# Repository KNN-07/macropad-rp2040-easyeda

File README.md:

# MACRO12 RP2040 macro pad for EasyEDA Pro

An editable EasyEDA Pro adaptation of the Adafruit MacroPad RP2040 Rev D: 12 MX-compatible hot-swap keys in a 3-column by 4-row layout, onboard RP2040, and USB-C.

Assembled Rev C prototype visualization using the actual board layout and CAD component models. Keycaps, knob, colors and displayed UI are illustrative. [Editable Blender scene, model sources and reproduction instructions](hardware/3d/).

**Rev C is released for first-article bare-board fabrication with the specified manufacturing and assembly constraints.** Native electrical DRC and schematic comparison pass; independent checks confirm all 76 nets, 338 physical pads and 171 drilled features. Nine intentional mechanical overlap findings remain documented individually in the [mechanical review](docs/mechanical-review.md). No physical board has been assembled or powered.

Download the [fabrication ZIP](fabrication/MACRO12-RevC-Gerber.zip) and read the [fabrication settings](docs/fabrication-notes.md) before ordering. The 1.6 mm board, precision LED milling and OLED/mounting controls are part of the design.

These previews are rendered from the released manufacturing data.

## Hardware

| Item | Design |
| --- | --- |
| Keys | 12, 19.05 mm pitch, MX-compatible hot-swap sockets |
| Controller | Onboard RP2040 with external flash |
| USB | HRO TYPE-C-31-M-12 USB-C connector |
| Encoder | Bourns PEC11R-4215F-S0024 with push switch |
| Board | 59.69 x 104.14 mm, two copper layers |
| Retained upstream features | 12 reverse-mount RGB LEDs, 16-pin folding OLED panel, speaker/amplifier, STEMMA QT |

The keys connect individually to GPIO1 through GPIO12; they are not a matrix. The electronic circuit and pin assignments come from the upstream Adafruit Rev D source. [QMK firmware with VIA support](firmware/README.md) provides four layers, remappable keys and encoder, RGB effects, and OLED status. Physical firmware testing remains pending.

## Open and edit

Import [MACRO12-RevC.epro](hardware/easyeda/MACRO12-RevC.epro) in EasyEDA Pro using **File > Import > EasyEDA (Professional)**. The archive includes the two schematic sheets, PCB, symbols, and footprints. Preserve the supplied footprints when importing; automatic footprint reassociation can change the design.

The EasyEDA project is the revised canonical design. The EAGLE files in `hardware/upstream/` are the unmodified upstream Rev D reference and do not contain the revised routing or Rev C footprint corrections. Earlier Rev B RC1 exports are superseded.

## Files

- [`hardware/easyeda/`](hardware/easyeda/): editable revised project.
- [`hardware/3d/`](hardware/3d/): assembled visualization, editable Blender scene, source CAD and render script.
- [`firmware/`](firmware/): QMK source, VIA definition, build workflow, flashing instructions, and first-article checks.
- [`fabrication/`](fabrication/): reviewed Gerber/Excellon ZIP and its ten unmodified manufacturing files.
- [`hardware/upstream/`](hardware/upstream/): original Rev D board and schematic, full upstream README, license, and its referenced product image.
- [`bom/`](bom/): reference BOM with Rev C part selections and retained upstream metadata. This is not an assembly-approved BOM or placement file.
- [`docs/release-validation.md`](docs/release-validation.md): completed checks, documented exceptions, and prototype validation limits.
- [`docs/mechanical-review.md`](docs/mechanical-review.md): drawing review, footprint corrections, and nine individual DRC dispositions.
- [`docs/assembly.md`](docs/assembly.md): required mounting and OLED-insulation controls.
- [`docs/fabrication-notes.md`](docs/fabrication-notes.md): board, milling, and plated-slot requirements.
- [`docs/modifications.md`](docs/modifications.md): changes from the upstream hardware.
- [`docs/checksums.sha256`](docs/checksums.sha256): file integrity hashes for the published snapshot.

## Attribution and license

Derived from [Adafruit MacroPad RP2040 PCB](https://github.com/adafruit/Adafruit-MacroPad-RP2040-PCB), designed by Limor Fried/Ladyada for Adafruit Industries, at commit `fdd7f2cb3bc2b3c7a9c0765780387647ea872141`.

The hardware design and modifications are distributed under **Creative Commons Attribution-ShareAlike 3.0 Unported**; see [LICENSE](LICENSE). The original [upstream README](hardware/upstream/README.md) is included in full as required by its redistribution notice. Hardware documentation uses the same license. The assembled visualization includes MIT-licensed Adafruit CAD; see [3D model licensing](hardware/3d/README.md#sources-and-licenses). Firmware, its documentation and tooling use **GPL-2.0-or-later**; see [firmware licensing](firmware/README.md#license-and-source). Adafruit and Raspberry Pi names identify the upstream design and component platform; this adaptation is not an official Adafruit product.

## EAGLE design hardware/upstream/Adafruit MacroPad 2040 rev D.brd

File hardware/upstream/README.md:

## Adafruit MacroPad RP2040 PCB

<a href="http://www.adafruit.com/products/5100"><br/>
Click here to purchase one from the Adafruit shop</a>

PCB files for the Adafruit MacroPad RP2040. 

Format is EagleCAD schematic and board layout
* https://www.adafruit.com/product/5100

### Description

Strap yourself in, we're launching in T-minus 10 seconds...Destination? A new Class M planet called MACROPAD! M here, stands for Microcontroller because this 3x4 keyboard controller features the newest technology from the Raspberry Pi sector: say hello to the RP2040. It's speedy little microcontroller with lots of GPIO pins and a 64 times more RAM than the Apollo Guidance Computer. We added 8 MB of flash memory for plenty of storage.

This is just the bare MACROPAD PCB assembly! Many folks in the mechanical keyboard community like to customize the keys and keycaps of their keebs, so this is sold 'bare bones' here. To use as a full product you'll need to add 12 MX-compatible key switches and matching key caps.

Get ready to upgrade your desk's mission control station with a CircuitPython or Arduino powered Macropad - complete with 12 buttons, OLED display, speaker and rotary encoder. Customize it for your spacecraft to help guide you through the great reaches of the unknown. (Or just have it type out your favorite emojis.)

Each of the 12 sockets can accept a Cherry MX-compatible key switch. No soldering required, just snap it in! Use any key switch you like - but we recommend ones with slots that will allow the matching twelve NeoPixels underneath to shine through.

This space-ship is also fitted with a 128x64 monochome OLED for a crisp heads-up display that can be used in Arduino or CircuitPython to display keymaps, stats, computer performance, etc. There's also a rotary encoder with push-button soldered in. Twist and turn it or push to change volume or monitor brightness or scroll: whatever you like! A tiny speaker can give audio feedback or play fun bleepy tunes.

Want to add more hardware? No worries - a STEMMA QT port on the side lets you connect any I2C add-on peripherals from the massive STEMMA QT / Qwiic family of plug in boards.

Please note, the RP2040 chip does not currently have QMK support - this macropad is designed to be programmed in Arduino or CircuitPython! If QMK eventually does add RP2040 as a supported chipset (no ETA and no plans that we know of), we'll update this page.

TL;DR?

* Raspberry Pi RP2040 Chip + 8MB Flash memory - Dual core Cortex M0+ at ~130MHz with 264KB or RAM. Runs CircuitPython, Arduino or MicroPython with ease and lots of space for development code and files
* USB C Connector for Power/Data - of course this can act as an HID device but also can be MIDI, UART, etc.
* 3x4 Mechanical key switch sockets - accepts any Cherry MX-compatible switches. Individually tied to GPIO pins (not matrix wired)
* One NeoPixel RGB LED per switch, on north side
* Rotary encoder, 20 detents per rotation, with push-switch on GPIO pin. Push switch is also used for entering bootloader mode when held down on power-up or reset.
* 128x64 SH1106 Monochrome OLED display - On high speed hardware SPI port for quick updates
* 8mm Speaker/Buzzer - With Class D amplifier and RC filter, can be used to make simple beeps and sounds effects.
* STEMMA QT Connector - Allows adding any I2C sensors/displays/devices with plug-and-play cables.
* Reset button - On the side, for quick restarting of code

### License

Adafruit invests time and resources providing this open source design, please support Adafruit and open-source hardware by purchasing products from [Adafruit](https://www.adafruit.com)!

Designed by Limor Fried/Ladyada for Adafruit Industries.

Creative Commons Attribution/Share-Alike, all text above must be included in any redistribution. 
See license.txt for additional details.

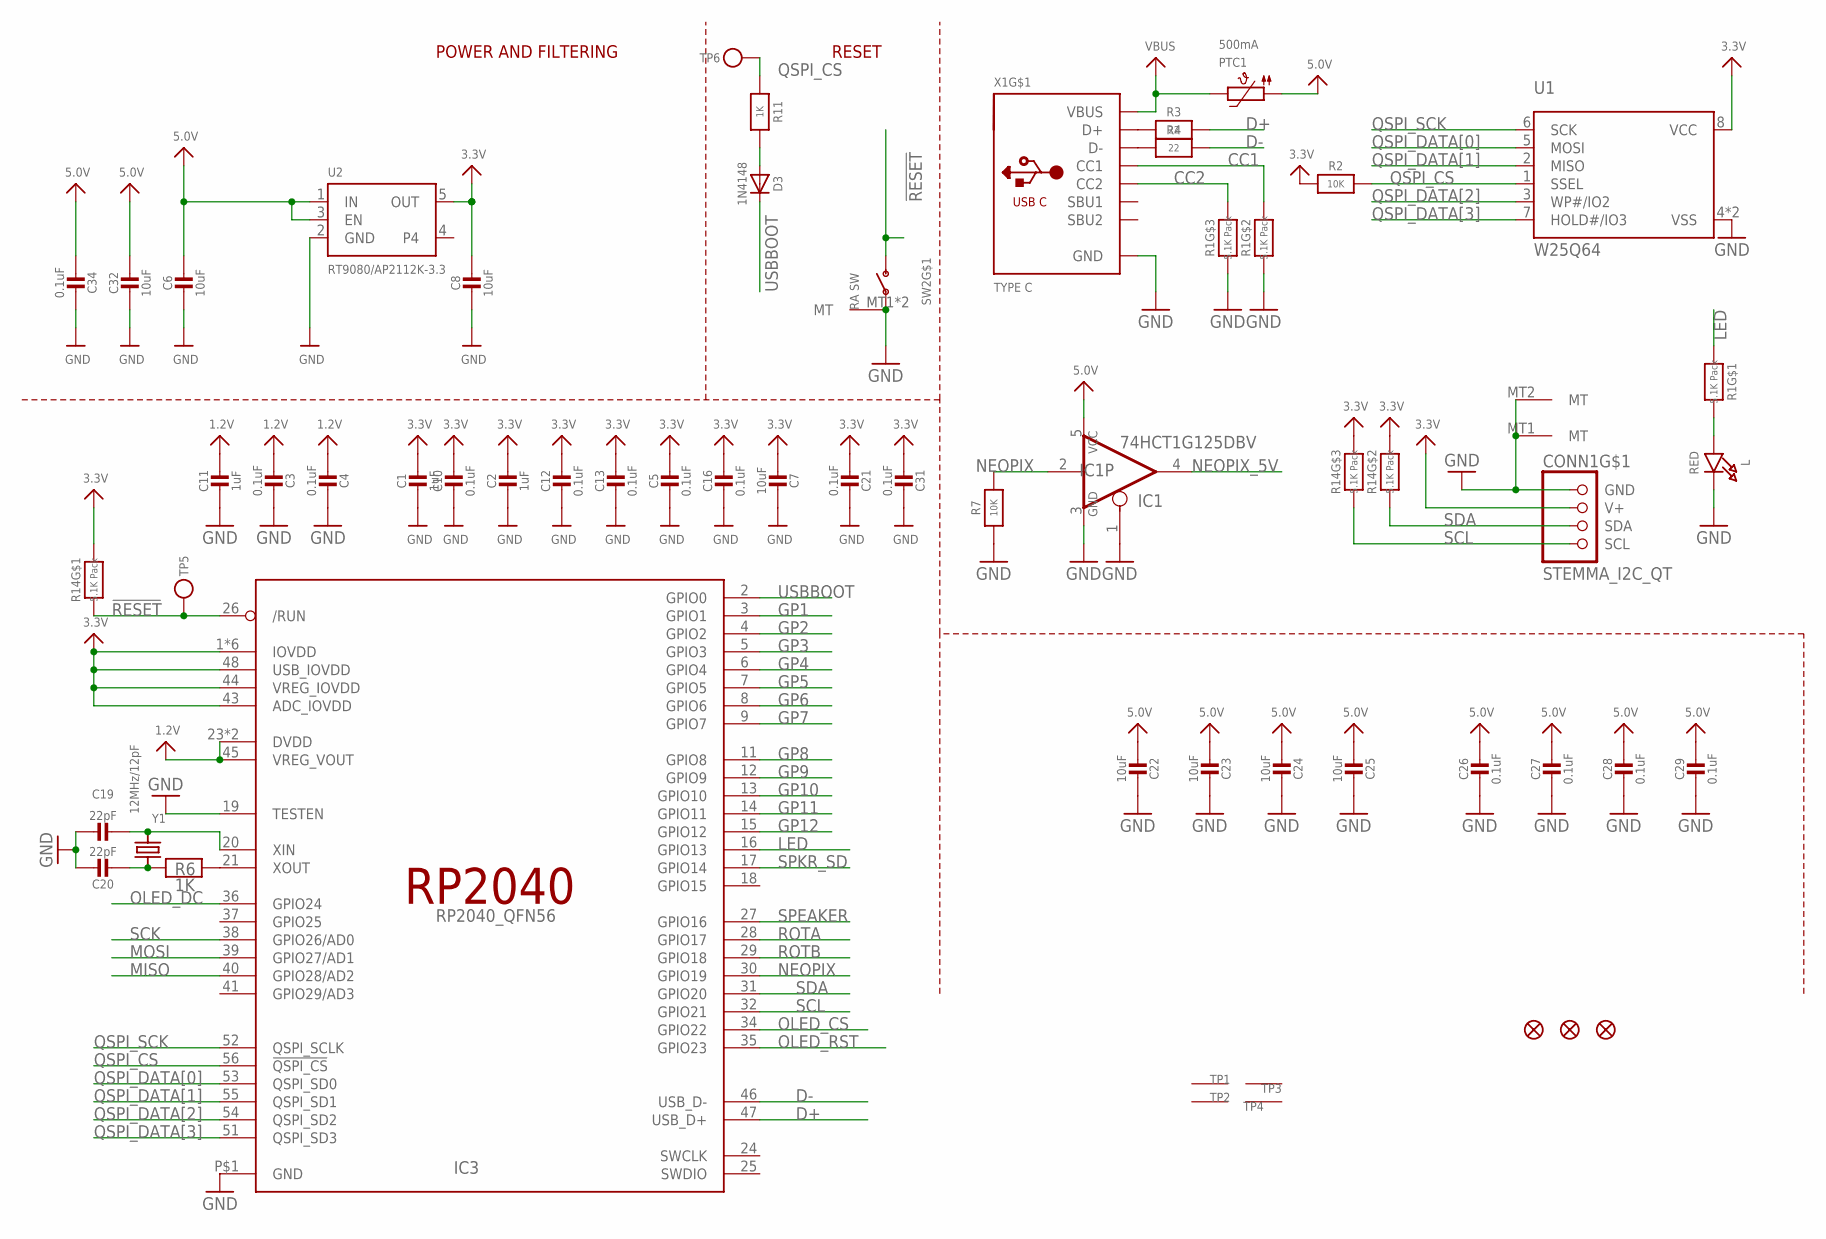
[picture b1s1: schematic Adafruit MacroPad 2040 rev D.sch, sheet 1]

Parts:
C1, C2, C11: 1uF; 0603-NO
C3, C4, C5, C10, C12, C13, C16, C21, C26, C27, C28, C29, C31, C34: 0.1uF; 0603-NO
C6, C7, C8, C22, C23, C24, C25, C32: 10uF; 0805-NO
C19, C20: 22pF; 0603-NO
CONN1: STEMMA_I2C_QT; JST_SH4
D3: 1N4148; SOD-323
IC1: 74HCT1G125DBV; SOT23-5
IC3: RP2040_QFN56; QFN56_7MM_REDUCEDEPAD
L: RED; CHIPLED_0603_NOOUTLINE
PTC1: 500mA; 0805-NO
R1, R14: 5.1K Pack; RESPACK_4X0603
R2, R7: 10K; 0603-NO
R3, R4: 22; 0603-NO
R6, R11: 1K; 0603-NO
SW2: RA SW; SPST_TACTILE_RA
TP1, TP2, TP3, TP4: SEWTAP_SMTNUTM3; SMT_NUT_3MM
TP5, TP6: TESTPOINTROUND1.5MMNO; TESTPOINT_ROUND_1.5MM_NO
U1: W25Q64; USON8_4X4
U2: RT9080/AP2112K-3.3; SOT23-5; JLC_ROTATION 0
U$34, U$35, U$80: FIDUCIAL_1MM
X1: TYPE C; USB_C_CUSB31-CFM2AX-01-X
Y1: 12MHz/12pF; CRYSTAL_2.5X2

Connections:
1.2V: C3.2, C4.2, C11.1, IC3.23 (DVDD), IC3.45 (VREG_VOUT), IC3.50 (DVDD)
3.3V: C1.1, C2.1, C5.1, C7.2, C8.1, C10.1, C12.1, C13.1, C16.1, C21.2, C31.2, CONN1.2 (V+), IC3.1 (IOVDD), IC3.10 (IOVDD), IC3.22 (IOVDD), IC3.33 (IOVDD), IC3.42 (IOVDD), IC3.43 (ADC_IOVDD), IC3.44 (VREG_IOVDD), IC3.48 (USB_IOVDD), IC3.49 (IOVDD), R2.1, R14.6 (2), R14.7 (2), R14.8 (2), U1.8 (VCC), U2.5 (OUT); also elsewhere on the board
5.0V: C6.1, C22.2, C23.2, C24.2, C25.2, C26.1, C27.1, C28.1, C29.1, C32.1, C34.2, IC1.5 (VCC), PTC1.1, U2.1 (IN), U2.3 (EN); also elsewhere on the board
!RESET: IC3.26 (/RUN), R14.1, SW2.2 (S), TP5.P$1
CC1: R1.7 (2), X1.A5 (CC1)
CC2: R1.6 (2), X1.B5 (CC2)
D+: IC3.47 (USB_D+), R3.2
D-: IC3.46 (USB_D-), R4.2
GND: C1.2, C2.2, C3.1, C4.1, C5.2, C6.2, C7.1, C8.2, C10.2, C11.2, C12.2, C13.2, C16.2, C19.1, C20.1, C21.1, C22.1, C23.1, C24.1, C25.1, C26.2, C27.2, C28.2, C29.2, C31.1, C32.2, C34.1, CONN1.1 (GND), CONN1.MT1 (MT), CONN1.MT2 (MT), IC1.1 (OE), IC1.3 (GND), IC3.19 (TESTEN), IC3.P$1 (GND), L.C, R1.2 (1), R1.3 (1), R7.1, SW2.1, SW2.MT1 (MT), SW2.MT2 (MT), U1.4 (VSS), U1.PAD (VSS), U2.2 (GND), X1.A1B12 (GND), X1.B1A12 (GND); also elsewhere on the board
GP1: IC3.3 (GPIO1); also elsewhere on the board
GP2: IC3.4 (GPIO2); also elsewhere on the board
GP3: IC3.5 (GPIO3); also elsewhere on the board
GP4: IC3.6 (GPIO4); also elsewhere on the board
GP5: IC3.7 (GPIO5); also elsewhere on the board
GP6: IC3.8 (GPIO6); also elsewhere on the board
GP7: IC3.9 (GPIO7); also elsewhere on the board
GP8: IC3.11 (GPIO8); also elsewhere on the board
GP9: IC3.12 (GPIO9); also elsewhere on the board
GP10: IC3.13 (GPIO10); also elsewhere on the board
GP11: IC3.14 (GPIO11); also elsewhere on the board
GP12: IC3.15 (GPIO12); also elsewhere on the board
LED: IC3.16 (GPIO13), R1.1
MISO: IC3.40 (GPIO28/AD2)
MOSI: IC3.39 (GPIO27/AD1); also elsewhere on the board
unnamed: R3.1, X1.A6 (D+), X1.B6 (D+)
unnamed: L.A, R1.8 (2)
unnamed: R4.1, X1.A7 (D-), X1.B7 (D-)
unnamed: D3.A, R11.2
unnamed: C19.2, IC3.20 (XIN), Y1.3 (2)
unnamed: C20.2, R6.1, Y1.1
unnamed: IC3.21 (XOUT), R6.2
NEOPIX: IC1.2 (I), IC3.30 (GPIO19), R7.2
NEOPIX_5V: IC1.4 (O); also elsewhere on the board
OLED_CS: IC3.34 (GPIO22); also elsewhere on the board
OLED_DC: IC3.36 (GPIO24); also elsewhere on the board
OLED_RST: IC3.35 (GPIO23); also elsewhere on the board
QSPI_CS: IC3.56 (!QSPI_CS), R2.2, R11.1, TP6.P$1, U1.1 (SSEL)
QSPI_DATA[0]: IC3.53 (QSPI_SD0), U1.5 (MOSI)
QSPI_DATA[1]: IC3.55 (QSPI_SD1), U1.2 (MISO)
QSPI_DATA[2]: IC3.54 (QSPI_SD2), U1.3 (WP#/IO2)
QSPI_DATA[3]: IC3.51 (QSPI_SD3), U1.7 (HOLD#/IO3)
QSPI_SCK: IC3.52 (QSPI_SCLK), U1.6 (SCK)
ROTA: IC3.28 (GPIO17); also elsewhere on the board
ROTB: IC3.29 (GPIO18); also elsewhere on the board
SCK: IC3.38 (GPIO26/AD0); also elsewhere on the board
SCL: CONN1.4 (SCL), IC3.32 (GPIO21), R14.3 (1)
SDA: CONN1.3 (SDA), IC3.31 (GPIO20), R14.2 (1)
SPEAKER: IC3.27 (GPIO16); also elsewhere on the board
SPKR_SD: IC3.17 (GPIO14); also elsewhere on the board
USBBOOT: D3.C, IC3.2 (GPIO0); also elsewhere on the board
VBUS: PTC1.2, X1.A4B9 (VBUS), X1.B4A9 (VBUS)

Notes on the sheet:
POWER AND FILTERING
RESET

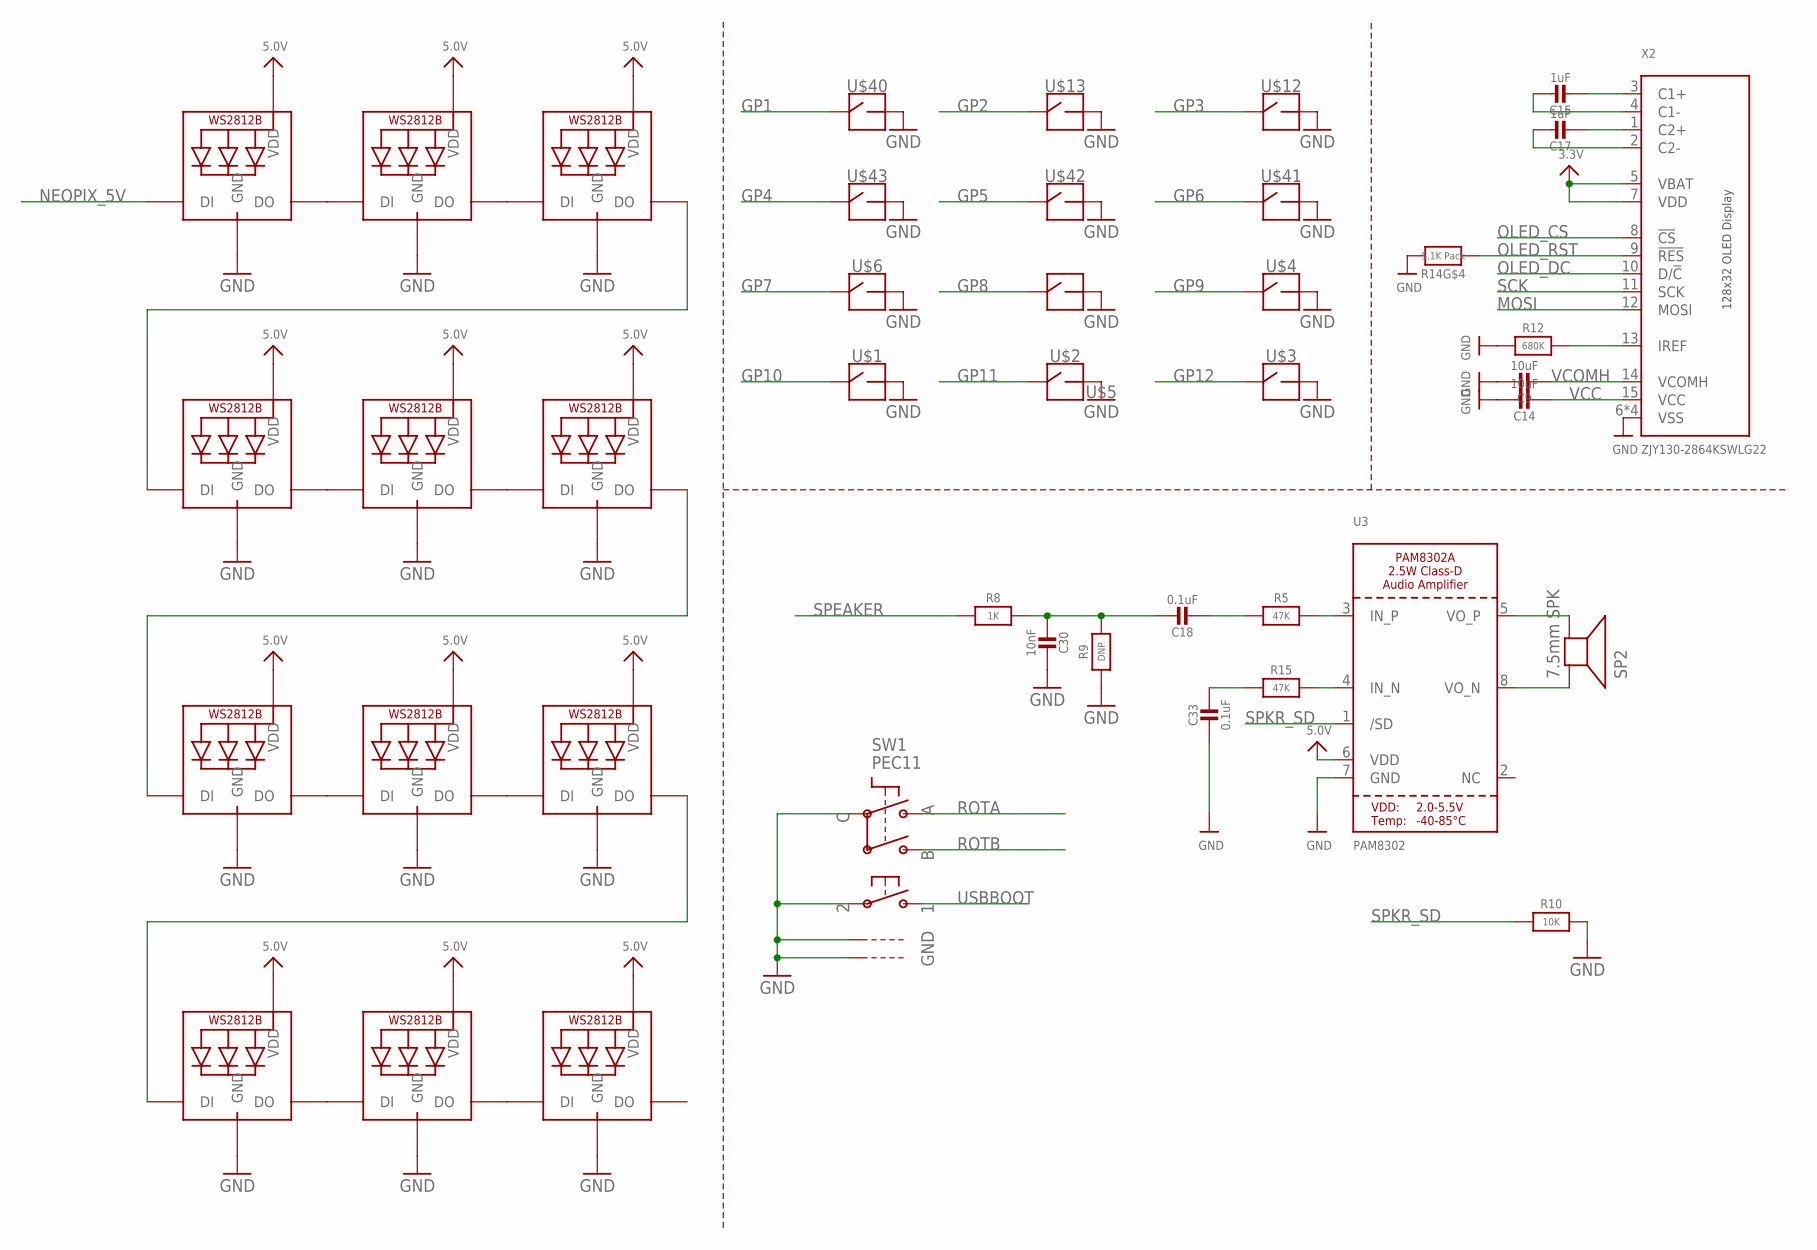
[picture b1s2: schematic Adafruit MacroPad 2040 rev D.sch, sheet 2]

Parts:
C9, C14: 10uF; 0805-NO
C15, C17: 1uF; 0603-NO
C18, C33: 0.1uF; 0603-NO
C30: 10nF; 0603-NO
LED1, LED2, LED3, LED4, LED5, LED6, LED7, LED8, LED9, LED10, LED11, LED12: WS2812B_SK6812E; NEO3535_REVERSE
R5, R15: 47K; 0603-NO
R8: 1K; 0603-NO
R9: DNP; 0603-NO
R10: 10K; 0603-NO
R12: 680K; 0603-NO
R14: 5.1K Pack; RESPACK_4X0603
SP2: 7.5mm SPK; BUZZER_SMT_7.5MM
SW1: PEC11; PEC11_SW_FIXED
U3: PAM8302; MSOP8_0.65MM
U$1, U$2, U$3, U$4, U$5, U$6, U$12, U$13, U$40, U$41, U$42, U$43: SOCKET; KAILH_SOCKET
X2: ZJY130-2864KSWLG22

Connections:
3.3V: X2.5 (VBAT), X2.7 (VDD); also elsewhere on the board
5.0V: LED1.1-VDD (VDD), LED2.1-VDD (VDD), LED3.1-VDD (VDD), LED4.1-VDD (VDD), LED5.1-VDD (VDD), LED6.1-VDD (VDD), LED7.1-VDD (VDD), LED8.1-VDD (VDD), LED9.1-VDD (VDD), LED10.1-VDD (VDD), LED11.1-VDD (VDD), LED12.1-VDD (VDD), U3.6 (VDD); also elsewhere on the board
GND: C9.1, C14.1, C30.1, C33.2, LED1.3-GND (GND), LED2.3-GND (GND), LED3.3-GND (GND), LED4.3-GND (GND), LED5.3-GND (GND), LED6.3-GND (GND), LED7.3-GND (GND), LED8.3-GND (GND), LED9.3-GND (GND), LED10.3-GND (GND), LED11.3-GND (GND), LED12.3-GND (GND), R9.1, R10.2, R12.1, R14.5 (2), SW1.P$2, SW1.P$C, SW1.P$GND1, SW1.P$GND2, U3.7 (GND), U$1.2, U$2.2, U$3.2, U$4.2, U$5.2, U$6.2, U$12.2, U$13.2, U$40.2, U$41.2, U$42.2, U$43.2, X2.6 (VSS), X2.16 (VSS), X2.SUPPORT1 (VSS), X2.SUPPORT2 (VSS); also elsewhere on the board
GP1: U$40.1; also elsewhere on the board
GP2: U$13.1; also elsewhere on the board
GP3: U$12.1; also elsewhere on the board
GP4: U$43.1; also elsewhere on the board
GP5: U$42.1; also elsewhere on the board
GP6: U$41.1; also elsewhere on the board
GP7: U$6.1; also elsewhere on the board
GP8: U$5.1; also elsewhere on the board
GP9: U$4.1; also elsewhere on the board
GP10: U$1.1; also elsewhere on the board
GP11: U$2.1; also elsewhere on the board
GP12: U$3.1; also elsewhere on the board
IN+: R5.2, U3.3 (IN_P)
IN-: R15.2, U3.4 (IN_N)
MOSI: X2.12 (MOSI); also elsewhere on the board
unnamed: C18.2, R5.1
unnamed: LED1.2-DOUT (DO), LED2.4-DIN (DI)
unnamed: LED2.2-DOUT (DO), LED3.4-DIN (DI)
unnamed: LED4.2-DOUT (DO), LED5.4-DIN (DI)
unnamed: LED5.2-DOUT (DO), LED6.4-DIN (DI)
unnamed: LED7.2-DOUT (DO), LED8.4-DIN (DI)
unnamed: LED8.2-DOUT (DO), LED9.4-DIN (DI)
unnamed: LED10.2-DOUT (DO), LED11.4-DIN (DI)
unnamed: LED11.2-DOUT (DO), LED12.4-DIN (DI)
unnamed: LED3.2-DOUT (DO), LED4.4-DIN (DI)
unnamed: LED6.2-DOUT (DO), LED7.4-DIN (DI)
unnamed: LED9.2-DOUT (DO), LED10.4-DIN (DI)
unnamed: R12.2, X2.13 (IREF)
unnamed: SP2.-, U3.5 (VO_P)
unnamed: C17.1, X2.2 (C2-)
unnamed: C17.2, X2.1 (C2+)
unnamed: C15.1, X2.4 (C1-)
unnamed: C15.2, X2.3 (C1+)
unnamed: SP2.+, U3.8 (VO_N)
unnamed: C33.1, R15.1
unnamed: C18.1, C30.2, R8.2, R9.2
NEOPIX_5V: LED1.4-DIN (DI); also elsewhere on the board
OLED_CS: X2.8 (!CS); also elsewhere on the board
OLED_DC: X2.10 (D/!C); also elsewhere on the board
OLED_RST: R14.4 (1), X2.9 (!RES); also elsewhere on the board
ROTA: SW1.P$A; also elsewhere on the board
ROTB: SW1.P$B; also elsewhere on the board
SCK: X2.11 (SCK); also elsewhere on the board
SPEAKER: R8.1; also elsewhere on the board
SPKR_SD: R10.1, U3.1 (/SD); also elsewhere on the board
USBBOOT: SW1.P$1; also elsewhere on the board
VCC: C14.2, X2.15 (VCC)
VCOMH: C9.2, X2.14 (VCOMH)

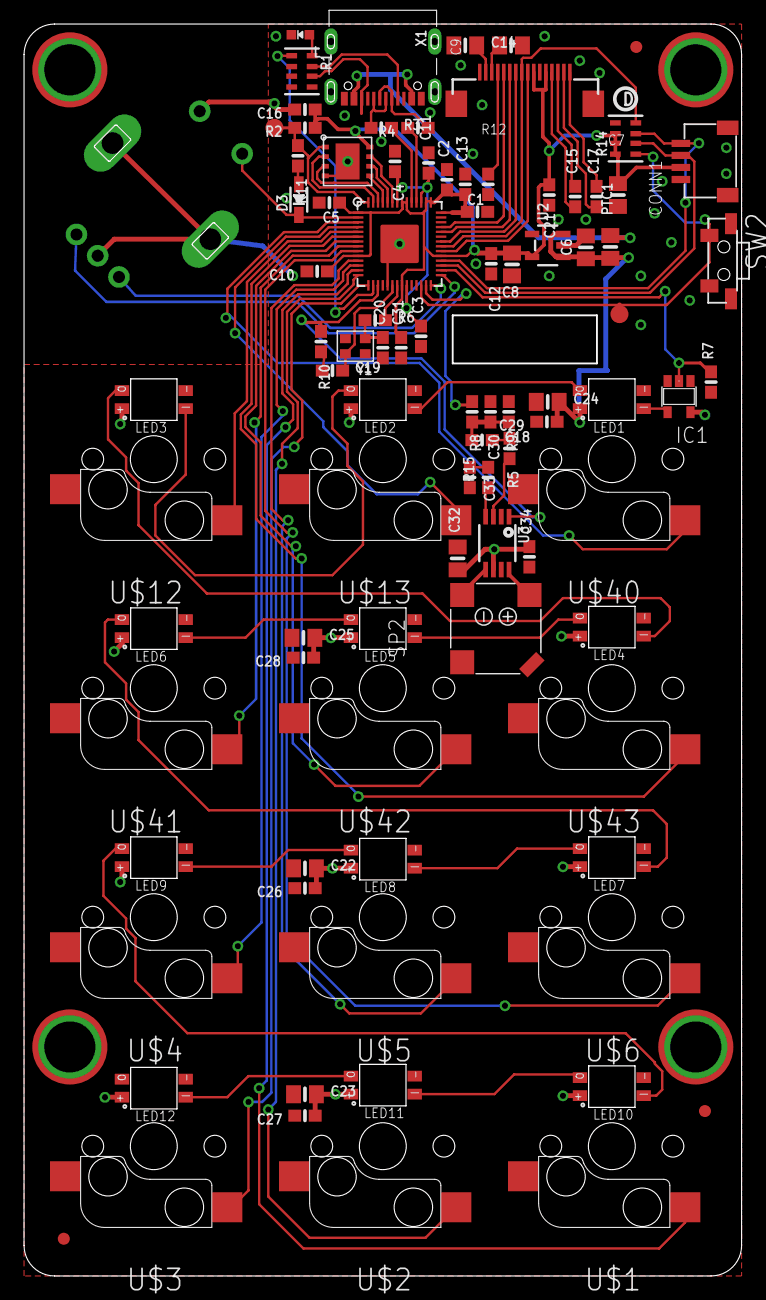
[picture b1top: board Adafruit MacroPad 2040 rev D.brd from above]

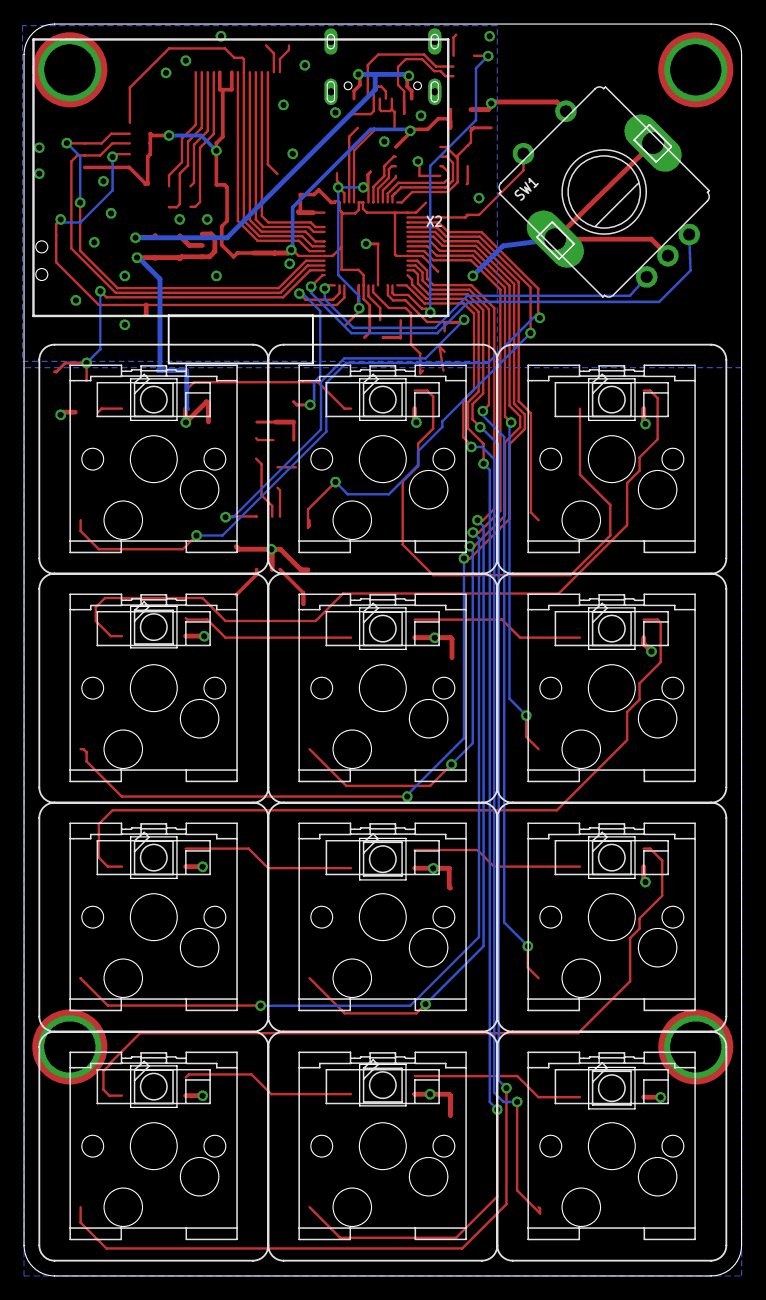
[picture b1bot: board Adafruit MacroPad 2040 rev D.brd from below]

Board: 2 copper layers, 59.7 x 104.1 mm, 99 parts (27 on the bottom side), 75 nets.

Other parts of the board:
U$78: MACROPAD_TOP
U$79: MACROPAD_BOTTOM
U$81: PCBFEAT-REV-040

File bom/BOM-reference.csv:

Reference,Value,Package,Library,CADSide,SelectedManufacturer,SelectedMPN,SupplierReference,AssemblyNote
U$1,SOCKET,KAILH_SOCKET,adafruit_electromech,Bottom,,,,"Combined footprint: switch/keycap bottom, hot-swap socket top; source reference only; verify selected socket part"
U$2,SOCKET,KAILH_SOCKET,adafruit_electromech,Bottom,,,,"Combined footprint: switch/keycap bottom, hot-swap socket top; source reference only; verify selected socket part"
U$3,SOCKET,KAILH_SOCKET,adafruit_electromech,Bottom,,,,"Combined footprint: switch/keycap bottom, hot-swap socket top; source reference only; verify selected socket part"
U$4,SOCKET,KAILH_SOCKET,adafruit_electromech,Bottom,,,,"Combined footprint: switch/keycap bottom, hot-swap socket top; source reference only; verify selected socket part"
U$5,SOCKET,KAILH_SOCKET,adafruit_electromech,Bottom,,,,"Combined footprint: switch/keycap bottom, hot-swap socket top; source reference only; verify selected socket part"
U$6,SOCKET,KAILH_SOCKET,adafruit_electromech,Bottom,,,,"Combined footprint: switch/keycap bottom, hot-swap socket top; source reference only; verify selected socket part"
C6,10uF,0805-NO,microbuilder,Top,,,,
C8,10uF,0805-NO,microbuilder,Top,,,,
L,RED,CHIPLED_0603_NOOUTLINE,microbuilder,Top,,,,
U2,RT9080/AP2112K-3.3,SOT23-5,adafruit_power,Top,,,,
IC1,74HCT1G125DBV,SOT23-5,74xx-little-us,Top,,,,
U1,W25Q64,USON8_4X4,microbuilder,Top,,,,
R2,10K,0603-NO,microbuilder,Top,,,,
C2,1uF,0603-NO,microbuilder,Top,,,,
C10,0.1uF,0603-NO,microbuilder,Top,,,,
IC3,RP2040_QFN56,QFN56_7MM_REDUCEDEPAD,adafruit_micro,Top,,,,
Y1,12MHz/12pF,CRYSTAL_2.5X2,microbuilder,Top,,,,
C3,0.1uF,0603-NO,microbuilder,Top,,,,
C4,0.1uF,0603-NO,microbuilder,Top,,,,
C11,1uF,0603-NO,microbuilder,Top,,,,
C12,0.1uF,0603-NO,microbuilder,Top,,,,
C13,0.1uF,0603-NO,microbuilder,Top,,,,
C16,0.1uF,0603-NO,microbuilder,Top,,,,
C19,22pF,0603-NO,microbuilder,Top,,,,
C20,22pF,0603-NO,microbuilder,Top,,,,
R6,1K,0603-NO,microbuilder,Top,,,,
R11,1K,0603-NO,microbuilder,Top,,,,
R3,22,0603-NO,microbuilder,Top,,,,
R4,22,0603-NO,microbuilder,Top,,,,
C1,1uF,0603-NO,microbuilder,Top,,,,
C5,0.1uF,0603-NO,microbuilder,Top,,,,
X1,TYPE-C-31-M-12,HRO_TYPE_C_31_M_12,adafruit_electromech,Top,HRO,TYPE-C-31-M-12,LCSC C165948 (upstream metadata),Rev C corrected lands/slots; control solder projection under OLED
U$12,SOCKET,KAILH_SOCKET,adafruit_electromech,Bottom,,,,"Combined footprint: switch/keycap bottom, hot-swap socket top; source reference only; verify selected socket part"
U$13,SOCKET,KAILH_SOCKET,adafruit_electromech,Bottom,,,,"Combined footprint: switch/keycap bottom, hot-swap socket top; source reference only; verify selected socket part"
U$40,SOCKET,KAILH_SOCKET,adafruit_electromech,Bottom,,,,"Combined footprint: switch/keycap bottom, hot-swap socket top; source reference only; verify selected socket part"
U$41,SOCKET,KAILH_SOCKET,adafruit_electromech,Bottom,,,,"Combined footprint: switch/keycap bottom, hot-swap socket top; source reference only; verify selected socket part"
U$42,SOCKET,KAILH_SOCKET,adafruit_electromech,Bottom,,,,"Combined footprint: switch/keycap bottom, hot-swap socket top; source reference only; verify selected socket part"
U$43,SOCKET,KAILH_SOCKET,adafruit_electromech,Bottom,,,,"Combined footprint: switch/keycap bottom, hot-swap socket top; source reference only; verify selected socket part"
SW1,PEC11R-4215F-S0024,PEC11R_4215F_S0024_13P2,adafruit_electromech,Bottom,Bourns,PEC11R-4215F-S0024,,Rev C only: 13.2 mm tab pitch; 4.0 x 2.0 mm plated slots
LED1,WS2812B_SK6812E,NEO3535_REVERSE,microbuilder,Bottom,OPSCO,SK6812MINI-E,,Reverse mount; aperture 3.5 x 3.8 mm; verify assembly side and pin 1
LED2,WS2812B_SK6812E,NEO3535_REVERSE,microbuilder,Bottom,OPSCO,SK6812MINI-E,,Reverse mount; aperture 3.5 x 3.8 mm; verify assembly side and pin 1
LED3,WS2812B_SK6812E,NEO3535_REVERSE,microbuilder,Bottom,OPSCO,SK6812MINI-E,,Reverse mount; aperture 3.5 x 3.8 mm; verify assembly side and pin 1
LED4,WS2812B_SK6812E,NEO3535_REVERSE,microbuilder,Bottom,OPSCO,SK6812MINI-E,,Reverse mount; aperture 3.5 x 3.8 mm; verify assembly side and pin 1
LED5,WS2812B_SK6812E,NEO3535_REVERSE,microbuilder,Bottom,OPSCO,SK6812MINI-E,,Reverse mount; aperture 3.5 x 3.8 mm; verify assembly side and pin 1
LED6,WS2812B_SK6812E,NEO3535_REVERSE,microbuilder,Bottom,OPSCO,SK6812MINI-E,,Reverse mount; aperture 3.5 x 3.8 mm; verify assembly side and pin 1
LED7,WS2812B_SK6812E,NEO3535_REVERSE,microbuilder,Bottom,OPSCO,SK6812MINI-E,,Reverse mount; aperture 3.5 x 3.8 mm; verify assembly side and pin 1
LED8,WS2812B_SK6812E,NEO3535_REVERSE,microbuilder,Bottom,OPSCO,SK6812MINI-E,,Reverse mount; aperture 3.5 x 3.8 mm; verify assembly side and pin 1
LED9,WS2812B_SK6812E,NEO3535_REVERSE,microbuilder,Bottom,OPSCO,SK6812MINI-E,,Reverse mount; aperture 3.5 x 3.8 mm; verify assembly side and pin 1
LED10,WS2812B_SK6812E,NEO3535_REVERSE,microbuilder,Bottom,OPSCO,SK6812MINI-E,,Reverse mount; aperture 3.5 x 3.8 mm; verify assembly side and pin 1
LED11,WS2812B_SK6812E,NEO3535_REVERSE,microbuilder,Bottom,OPSCO,SK6812MINI-E,,Reverse mount; aperture 3.5 x 3.8 mm; verify assembly side and pin 1
LED12,WS2812B_SK6812E,NEO3535_REVERSE,microbuilder,Bottom,OPSCO,SK6812MINI-E,,Reverse mount; aperture 3.5 x 3.8 mm; verify assembly side and pin 1
SW2,RA SW,SPST_TACTILE_RA,adafruit_electromech,Top,G-Switch,GT-TC054B-H035-L1,LCSC C778159 (upstream metadata),Rev C symmetric mounting lands; preserve reviewed signal lands and peg holes
CONN1,STEMMA_I2C_QT,JST_SH4,adafruit_electromech,Top,,,,
C7,10uF,0805-NO,microbuilder,Top,,,,
C9,10uF,0805-NO,microbuilder,Top,,,,
R12,680K,0603-NO,microbuilder,Top,,,,
C21,0.1uF,0603-NO,microbuilder,Top,,,,
D3,1N4148,SOD-323,microbuilder,Top,,,,
TP1,SEWTAP_SMTNUTM3,SMT_NUT_3MM,adafruit_electromech,Top,Adafruit,4207 or drawing-equivalent M3 solderable nut,Adafruit 4207,Top-side shoulder; nose <=1.5 mm; bottom flush/recessed; see docs/assembly.md
TP2,SEWTAP_SMTNUTM3,SMT_NUT_3MM,adafruit_electromech,Top,Adafruit,4207 or drawing-equivalent M3 solderable nut,Adafruit 4207,Top-side shoulder; nose <=1.5 mm; bottom flush/recessed; see docs/assembly.md
TP3,SEWTAP_SMTNUTM3,SMT_NUT_3MM,adafruit_electromech,Top,Adafruit,4207 or drawing-equivalent M3 solderable nut,Adafruit 4207,Top-side shoulder; nose <=1.5 mm; bottom flush/recessed; see docs/assembly.md
TP4,SEWTAP_SMTNUTM3,SMT_NUT_3MM,adafruit_electromech,Top,Adafruit,4207 or drawing-equivalent M3 solderable nut,Adafruit 4207,Top-side shoulder; nose <=1.5 mm; bottom flush/recessed; see docs/assembly.md
X2,ZJY130-2864KSWLG22,ZJY130-2864KSWLG22,adafruit_display,Bottom,Zhongjingyuan,ZJY130-2864KSWLG22,,16-pin folding panel; matching flex connector/process required; >=0.5 mm insulating spacer
C14,10uF,0805-NO,microbuilder,Top,,,,
C15,1uF,0603-NO,microbuilder,Top,,,,
C17,1uF,0603-NO,microbuilder,Top,,,,
R14,5.1K Pack,RESPACK_4X0603,microbuilder,Top,,,,
R1,5.1K Pack,RESPACK_4X0603,microbuilder,Top,,,,
SP2,7.5mm SPK,BUZZER_SMT_7.5MM,microbuilder,Top,,,,
C18,0.1uF,0603-NO,microbuilder,Top,,,,
R5,47K,0603-NO,microbuilder,Top,,,,
R10,10K,0603-NO,microbuilder,Top,,,,
R7,10K,0603-NO,microbuilder,Top,,,,
C22,10uF,0805-NO,microbuilder,Top,,,,
C23,10uF,0805-NO,microbuilder,Top,,,,
C24,10uF,0805-NO,microbuilder,Top,,,,
C25,10uF,0805-NO,microbuilder,Top,,,,
C26,0.1uF,0603-NO,microbuilder,Top,,,,
C27,0.1uF,0603-NO,microbuilder,Top,,,,
C28,0.1uF,0603-NO,microbuilder,Top,,,,
C29,0.1uF,0603-NO,microbuilder,Top,,,,
R8,1K,0603-NO,microbuilder,Top,,,,
C30,10nF,0603-NO,microbuilder,Top,,,,
R9,DNP,0603-NO,microbuilder,Top,,,,DNP in source; do not populate by default
C31,0.1uF,0603-NO,microbuilder,Top,,,,
TP5,,TESTPOINT_ROUND_1.5MM_NO,microbuilder,Top,,,,
TP6,,TESTPOINT_ROUND_1.5MM_NO,microbuilder,Top,,,,
R15,47K,0603-NO,microbuilder,Top,,,,
C33,0.1uF,0603-NO,microbuilder,Top,,,,
U3,PAM8302,MSOP8_0.65MM,microbuilder,Top,,,,
PTC1,500mA,0805-NO,microbuilder,Top,,,,
C32,10uF,0805-NO,microbuilder,Top,,,,
C34,0.1uF,0603-NO,microbuilder,Top,,,,

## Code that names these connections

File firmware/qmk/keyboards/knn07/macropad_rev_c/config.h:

/* Copyright 2022 Jose Pablo Ramirez <jp.ramangulo@gmail.com>
 *
 * This program is free software: you can redistribute it and/or modify
 * it under the terms of the GNU General Public License as published by
 * the Free Software Foundation, either version 2 of the License, or
 * (at your option) any later version.
 *
 * This program is distributed in the hope that it will be useful,
 * but WITHOUT ANY WARRANTY; without even the implied warranty of
 * MERCHANTABILITY or FITNESS FOR A PARTICULAR PURPOSE.  See the
 * GNU General Public License for more details.
 *
 * You should have received a copy of the GNU General Public License
 * along with this program.  If not, see <http://www.gnu.org/licenses/>.
 */

#pragma once

/* The same 128x64 SPI SH1106 interface as the Adafruit MacroPad. */
#define OLED_DISPLAY_128X64
#define OLED_IC OLED_IC_SH1106
#define OLED_DC_PIN GP24
#define OLED_CS_PIN GP22
#define OLED_RST_PIN GP23
#define OLED_COLUMN_OFFSET 2
#define OLED_SPI_DIVISOR 4
#define OLED_TIMEOUT 60000
#define OLED_UPDATE_INTERVAL 100

#define SPI_DRIVER SPID1
#define SPI_SCK_PIN GP26
#define SPI_MOSI_PIN GP27
/* GP28 is named MISO, but the write-only OLED has no MISO connection. */
#define SPI_MISO_PIN GP28

/* Double-tap the side reset button within 500 ms to enter RPI-RP2. */
#define RP2040_BOOTLOADER_DOUBLE_TAP_RESET
#define RP2040_BOOTLOADER_DOUBLE_TAP_RESET_LED GP13
#define RP2040_BOOTLOADER_DOUBLE_TAP_RESET_TIMEOUT 500U

/* Explicitly retain QMK's conservative 2 MiB flash window on the 8 MiB U1.
 * Reserve the final 8 KiB in that window for 4 KiB logical EEPROM. */
#define WEAR_LEVELING_RP2040_FLASH_SIZE (2 * 1024 * 1024)
#define WEAR_LEVELING_BACKING_SIZE 8192
#define WEAR_LEVELING_LOGICAL_SIZE 4096

/* QMK defaults DYNAMIC_KEYMAP_LAYER_COUNT to 4, matching these presets. */

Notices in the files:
parts and their libraries:
microbuilder: This work is placed in the public domain, and may be freely used for commercial and non-commercial work with the following conditions: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
